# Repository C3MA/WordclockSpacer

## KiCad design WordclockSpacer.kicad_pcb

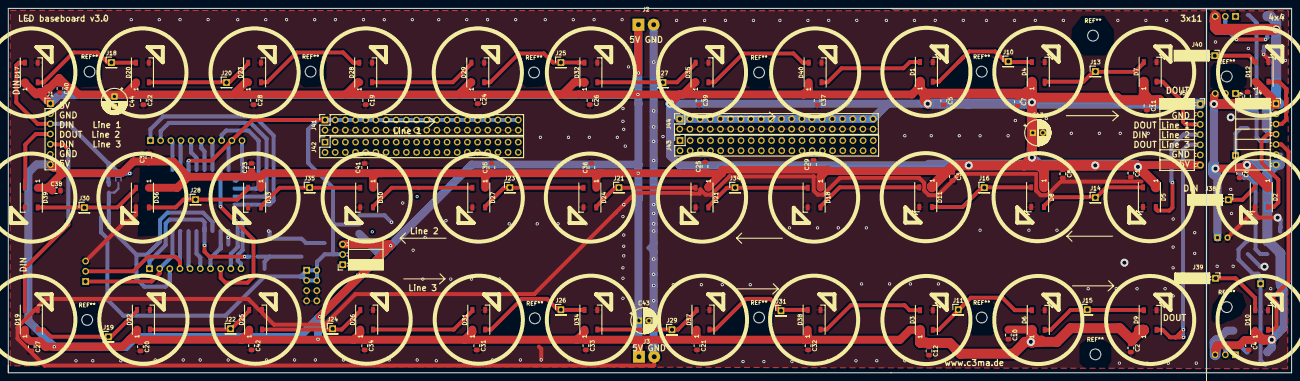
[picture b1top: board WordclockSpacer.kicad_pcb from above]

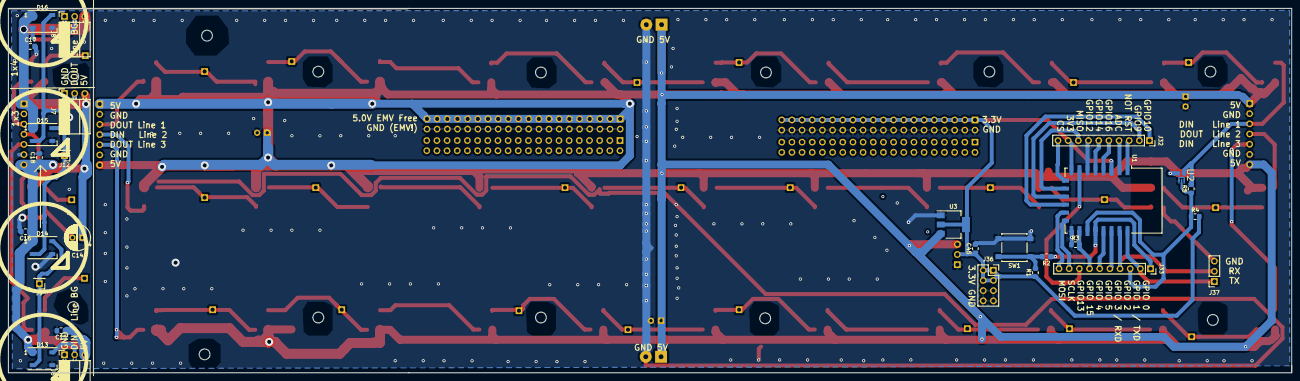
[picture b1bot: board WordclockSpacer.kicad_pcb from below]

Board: 2 copper layers, 320.5 x 91.0 mm, 138 parts (28 on the bottom side), 69 nets.

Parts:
C1, C2, C3, C4, C5, C6, C7, C8, C9, C10, C11, C12, C15, C16, C17, C18, C19, C20, C21, C22, C23, C24, C25, C26, C27, C28, C29, C30, C31, C32, C33, C34, C35, C36, C37, C38, C39, C40, C41, C42, C45: 100n; C_0805_2012Metric_Pad1.15x1.40mm_HandSolder
C13, C14, C43, C44: 100u; CP_Radial_D6.3mm_P2.50mm
D1, D2, D3, D4, D5, D6, D7, D8, D9, D10, D11, D12, D13, D14, D15, D16, D17, D18, D19, D20, D21, D22, D23, D24, D25, D26, D27, D28, D29, D30, D31, D32, D33, D34, D35, D36, D37, D38, D39, D40: WS2812B; LED_WS2812B_PLCC4_5.0x5.0mm_P3.2mmMitEcke
J1: Input; PinHeader_1x07_P2.54mm_Vertical
J2, J3: Conn_01x02_Male; SolderWirePad_1x02_P3.81mm_Drill1.2mm
J4: Output; PinSocket_1x07_P2.54mm_Horizontal
J5: Middle Out; PinSocket_1x07_P2.54mm_Horizontal
J6: Back Line In; PinSocket_1x03_P2.54mm_Horizontal
J7: Back Line Out middle; PinSocket_1x03_P2.54mm_Horizontal
J8: Back Line Out; PinSocket_1x03_P2.54mm_Horizontal
J9: LED1Back; PinHeader_1x01_P2.54mm_Vertical
J10, J18, J25: LED1; PinHeader_1x01_P2.54mm_Vertical
J11, J19, J26: LED7; PinHeader_1x01_P2.54mm_Vertical
J12: LED2Back; PinHeader_1x01_P2.54mm_Vertical
J13, J20, J27: LED2; PinHeader_1x01_P2.54mm_Vertical
J14, J21, J28: LED5; PinHeader_1x01_P2.54mm_Vertical
J15, J22, J29: LED8; PinHeader_1x01_P2.54mm_Vertical
J16, J23, J30: LED6; PinHeader_1x01_P2.54mm_Vertical
J17: Conn_01x03_Female; PinSocket_1x03_P2.54mm_Horizontal
J24, J31: LED9; PinHeader_1x01_P2.54mm_Vertical
J32, J33: Conn_01x10; PinSocket_1x10_P2.54mm_Vertical
J34, J35: LED4; PinHeader_1x01_P2.54mm_Vertical
J36: Conn_02x04_Odd_Even; PinSocket_2x04_P2.54mm_Vertical
J37: Conn_01x03_Female; PinSocket_1x03_P2.54mm_Vertical
J38: LED_OUT; PinSocket_1x01_P2.54mm_Horizontal
J39, J40: LED_IN; PinSocket_1x01_P2.54mm_Horizontal
J41, J44: Conn_02x20_Odd_Even; PinSocket_2x20_P2.54mm_Vertical
J42, J43: Conn_02x20_Counter_Clockwise; PinSocket_2x20_P2.54mm_Vertical
R1: 1k; R_0805_2012Metric_Pad1.15x1.40mm_HandSolder
R2, R4: 10k; R_0805_2012Metric_Pad1.15x1.40mm_HandSolder
R3: 2k2; R_0805_2012Metric_Pad1.15x1.40mm_HandSolder
R5: 0; R_0805_2012Metric_Pad1.15x1.40mm_HandSolder
SW1: SW_Push; SW_SPST_B3S-1000
U1: ESP-12E
U2: 74HCT1G125GW; SOT65P210X110-5N
U3: AMS1117-3.3; SOT-223-3_TabPin2

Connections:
+3V3: C45.1, J17.2, J32.9, J36.1, J36.2, J36.3, J36.4, J41.1, J41.3, J41.5, J41.7, J41.9, J41.11, J41.13, J41.15, J41.17, J41.19, J41.21, J41.23, J41.25, J41.27, J41.29, J41.31, J41.33, J41.35, J41.37, J41.39, R1.1, R4.2, U1.3 (EN), U1.8 (VCC), U3.2 (VO)
+5V: C1.1, C2.1, C3.1, C4.1, C5.1, C6.1, C7.1, C8.1, C9.1, C10.1, C11.1, C12.1, C13.1, C14.1, C15.1, C16.1, C17.1, C18.1, C19.1, C20.1, C21.1, C22.1, C23.1, C24.1, C25.1, C26.1, C27.1, C28.1, C29.1, C30.1, C31.1, C32.1, C33.1, C34.1, C35.1, C36.1, C37.1, C38.1, C39.1, C40.1, C41.1, C42.1, C43.1, C44.1, D1.1 (VDD), D2.1 (VDD), D3.1 (VDD), D4.1 (VDD), D5.1 (VDD), D6.1 (VDD), D7.1 (VDD), D8.1 (VDD), D9.1 (VDD), D10.1 (VDD), D11.1 (VDD), D12.1 (VDD), D13.1 (VDD), D14.1 (VDD), D15.1 (VDD), D16.1 (VDD), D17.1 (VDD), D18.1 (VDD), D19.1 (VDD), D20.1 (VDD), D21.1 (VDD), D22.1 (VDD), D23.1 (VDD), D24.1 (VDD), D25.1 (VDD), D26.1 (VDD), D27.1 (VDD), D28.1 (VDD), D29.1 (VDD), D30.1 (VDD), D31.1 (VDD), D32.1 (VDD), D33.1 (VDD), D34.1 (VDD), D35.1 (VDD), D36.1 (VDD), D37.1 (VDD), D38.1 (VDD), D39.1 (VDD), D40.1 (VDD), J1.1, J1.7, J2.1, J3.1, J4.1, J4.7, J5.1, J5.7, J6.3, J7.3, J8.3, J17.3, J44.1, J44.3, J44.5, J44.7, J44.9, J44.11, J44.13, J44.15, J44.17, J44.19, J44.21, J44.23, J44.25, J44.27, J44.29, J44.31, J44.33, J44.35, J44.37, J44.39, U2.5 (VCC), U3.3 (VI)
DIN_1_LINE1: D17.4 (DIN), J1.3, R5.2, U2.4 (Y)
DIN_1_LINE3: D19.4 (DIN), J1.5
DIN_2_LINE2: D11.2 (DOUT), D18.4 (DIN)
DIN_LINE2: D2.4 (DIN), J4.4
DIN_SHORT_LINE2: D5.4 (DIN), J5.4
DOUT_1_LINE2: D39.2 (DOUT), J1.4
DOUT_2_LINE1: D1.4 (DIN), D40.2 (DOUT)
DOUT_2_LINE3: D3.4 (DIN), D38.2 (DOUT)
DOUT_LINE3: D10.2 (DOUT), J4.5
DOUT_SHORT_LINE1: D7.2 (DOUT), J5.3
DOUT_SHORT_LINE3: D9.2 (DOUT), J5.5
GND: C1.2, C2.2, C3.2, C4.2, C5.2, C6.2, C7.2, C8.2, C9.2, C10.2, C11.2, C12.2, C13.2, C14.2, C15.2, C16.2, C17.2, C18.2, C19.2, C20.2, C21.2, C22.2, C23.2, C24.2, C25.2, C26.2, C27.2, C28.2, C29.2, C30.2, C31.2, C32.2, C33.2, C34.2, C35.2, C36.2, C37.2, C38.2, C39.2, C40.2, C41.2, C42.2, C43.2, C44.2, C45.2, D1.3 (VSS), D2.3 (VSS), D3.3 (VSS), D4.3 (VSS), D5.3 (VSS), D6.3 (VSS), D7.3 (VSS), D8.3 (VSS), D9.3 (VSS), D10.3 (VSS), D11.3 (VSS), D12.3 (VSS), D13.3 (VSS), D14.3 (VSS), D15.3 (VSS), D16.3 (VSS), D17.3 (VSS), D18.3 (VSS), D19.3 (VSS), D20.3 (VSS), D21.3 (VSS), D22.3 (VSS), D23.3 (VSS), D24.3 (VSS), D25.3 (VSS), D26.3 (VSS), D27.3 (VSS), D28.3 (VSS), D29.3 (VSS), D30.3 (VSS), D31.3 (VSS), D32.3 (VSS), D33.3 (VSS), D34.3 (VSS), D35.3 (VSS), D36.3 (VSS), D37.3 (VSS), D38.3 (VSS), D39.3 (VSS), D40.3 (VSS), J1.2, J1.6, J2.2, J3.2, J4.2, J4.6, J5.2, J5.6, J6.1, J7.1, J8.1, J17.1, J32.7, J36.5, J36.6, J36.7, J36.8, J37.3, J41.2, J41.4, J41.6, J41.8, J41.10, J41.12, J41.14, J41.16, J41.18, J41.20, J41.22, J41.24, J41.26, J41.28, J41.30, J41.32, J41.34, J41.36, J41.38, J41.40, J44.2, J44.4, J44.6, J44.8, J44.10, J44.12, J44.14, J44.16, J44.18, J44.20, J44.22, J44.24, J44.26, J44.28, J44.30, J44.32, J44.34, J44.36, J44.38, J44.40, R3.1, SW1.2, U1.6 (GPIO12), U1.15 (GND), U2.1 (~OE), U2.3 (GND), U3.1 (GND)
unnamed: D1.2 (DOUT), D4.4 (DIN), J10.1
unnamed: D2.2 (DOUT), J38.1
unnamed: D3.2 (DOUT), D6.4 (DIN), J11.1
unnamed: D4.2 (DOUT), D7.4 (DIN), J13.1
unnamed: D5.2 (DOUT), D8.4 (DIN), J14.1
unnamed: D6.2 (DOUT), D9.4 (DIN), J15.1
unnamed: D10.4 (DIN), J39.1
unnamed: D8.2 (DOUT), D11.4 (DIN), J16.1
unnamed: D12.2 (DOUT), J4.3
unnamed: D12.4 (DIN), J40.1
unnamed: D13.2 (DOUT), D14.4 (DIN), J9.1
unnamed: D13.4 (DIN), J6.2
unnamed: D14.2 (DOUT), D15.4 (DIN), J12.1
unnamed: D15.2 (DOUT), D16.4 (DIN), J7.2
unnamed: D16.2 (DOUT), J8.2
unnamed: D17.2 (DOUT), D20.4 (DIN), J18.1
unnamed: D18.2 (DOUT), D21.4 (DIN), J34.1
unnamed: D19.2 (DOUT), D22.4 (DIN), J19.1
unnamed: D20.2 (DOUT), D23.4 (DIN), J20.1
unnamed: D21.2 (DOUT), D24.4 (DIN), J21.1
unnamed: D22.2 (DOUT), D25.4 (DIN), J22.1
unnamed: D23.2 (DOUT), D28.4 (DIN)
unnamed: D24.2 (DOUT), D27.4 (DIN), J23.1
unnamed: D25.2 (DOUT), D26.4 (DIN), J24.1
unnamed: D26.2 (DOUT), D31.4 (DIN)
unnamed: D27.2 (DOUT), D30.4 (DIN)
unnamed: D28.2 (DOUT), D29.4 (DIN)
unnamed: D29.2 (DOUT), D32.4 (DIN), J25.1
unnamed: D30.2 (DOUT), D33.4 (DIN), J35.1
unnamed: D31.2 (DOUT), D34.4 (DIN), J26.1
unnamed: D32.2 (DOUT), D35.4 (DIN), J27.1
unnamed: D33.2 (DOUT), D36.4 (DIN), J28.1
unnamed: D34.2 (DOUT), D37.4 (DIN), J29.1
unnamed: D35.2 (DOUT), D40.4 (DIN)
unnamed: D36.2 (DOUT), D39.4 (DIN), J30.1
unnamed: D37.2 (DOUT), D38.4 (DIN), J31.1
unnamed: J32.1, U1.12 (GPIO10)
unnamed: J32.2, U1.11 (GPIO9)
unnamed: J32.3, U1.1 (~RST)
unnamed: J32.4, U1.2 (ADC)
unnamed: J32.5, U1.4 (GPIO16)
unnamed: J32.6, U1.5 (GPIO14)
unnamed: J32.8, U1.10 (MISO)
unnamed: J32.10, U1.9 (CS0)
unnamed: J33.1, R2.1, U1.18 (GPIO0)
unnamed: J33.2, J37.1, U1.22 (GPIO1/TXD)
unnamed: J33.3, R4.1, R5.1, U1.17 (GPIO2), U2.2 (A)
unnamed: J33.4, J37.2, U1.21 (GPIO3/RXD)
unnamed: J33.5, U1.20 (GPIO5)
unnamed: J33.6, U1.19 (GPIO4)
unnamed: J33.7, R3.2, U1.16 (GPIO15)
unnamed: J33.8, U1.7 (GPIO13)
unnamed: J33.9, U1.14 (SCLK)
unnamed: J33.10, U1.13 (MOSI)
unnamed: R1.2, R2.2, SW1.1

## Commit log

2019-03-01 KiCAD project
2019-03-06 improved footprint
2019-03-06 GPIO Names fixed
2019-05-03 V3 Alpha
2019-05-15 no Alpha. it is V3
2022-09-28 V3.0 added AMS1117
2022-09-28 Started script, generating Gcode file
2022-09-30 First two rows are generated
2022-09-30 Set the drillspeed
2022-09-30 Project starts at the corner of the first circle
2022-09-30 Active spindle
2022-09-30 repeat wholes on Z axis, add header on top
2022-10-14 Show offset after generation
2022-10-14 Travel height, neeeded at the end; removed redudant speed definition
2022-10-14 Bigger diameter; 2mm at once
2022-10-14 One mm is max
2022-10-14 Increase feedrate
